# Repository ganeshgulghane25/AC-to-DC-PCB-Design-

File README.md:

# AC-to-DC-PCB-Design-
PCB design of an AC to DC converter using rectifier, filter, and voltage regulator circuits. Designed on KiCad with optimized layout for stable DC power output.

# AC to DC Converter (Bridge Rectifier)

A simple AC to DC conversion circuit designed in **KiCad**, consisting of a full-bridge rectifier using 1N4007 diodes, filter capacitor, and an indicator LED. This circuit converts AC input to a DC output suitable for low-power applications.

---

## 🔧 Circuit Components
- 4 × 1N4007 Diodes (Full Bridge Rectifier)
- Electrolytic Capacitor (Filter)
- LED Indicator
- Current Limiting Resistor
- Screw Terminal Inputs/Outputs

---

## ⚙️ Working Principle

The AC input is fed into a **bridge rectifier**, which converts alternating current into pulsating DC.  
A filter capacitor smooths the pulsations, producing a more stable DC voltage.  
An LED indicator is included to show circuit output status.

---

## 🧠 Skills Demonstrated
- KiCad schematic design
- Understanding of rectifier circuits
- Power electronics basics
- PCB-ready layout planning

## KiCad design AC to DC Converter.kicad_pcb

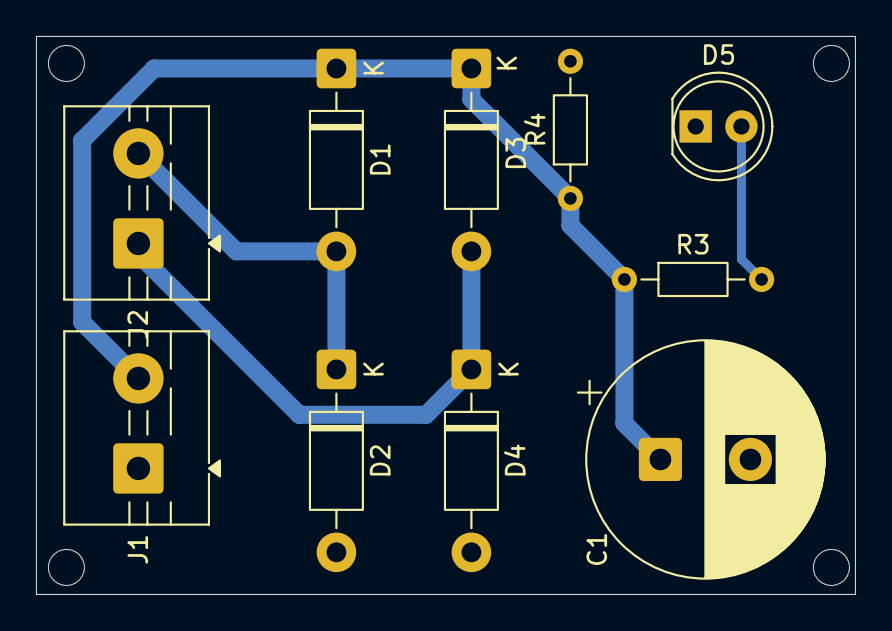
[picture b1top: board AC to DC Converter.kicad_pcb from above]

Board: 2 copper layers, 45.5 x 31.0 mm, 10 parts (0 on the bottom side), 5 nets.

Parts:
C1: 1000uF; CP_Radial_D13.0mm_P5.00mm
D1, D2, D3, D4: 1N4007; D_DO-41_SOD81_P10.16mm_Horizontal
D5: LED; LED_D5.0mm
J1, J2: Screw_Terminal; TerminalBlock_MaiXu_MX126-5.0-02P_1x02_P5.00mm
R3: 2.2K; R_Axial_DIN0204_L3.6mm_D1.6mm_P7.62mm_Horizontal
R4: 10K; R_Axial_DIN0204_L3.6mm_D1.6mm_P7.62mm_Horizontal

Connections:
/+VE: C1.1, D1.1 (K), D3.1 (K), J1.2, R3.1, R4.1
GND: C1.2, D2.2 (A), D4.2 (A), D5.1 (K), J1.1, R4.2
unnamed: D1.2 (A), D2.1 (K), J2.2
unnamed: D3.2 (A), D4.1 (K), J2.1
unnamed: D5.2 (A), R3.2

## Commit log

2025-12-06 This is schematic of the project.
